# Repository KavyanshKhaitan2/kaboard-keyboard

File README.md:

# Kaboard!
[[ Showcase video ]](https://youtu.be/ID2R_xTHKyI)

_Yet another mechanical keyboard_

This is the first full-size keyboard I built!

It is a full-size mechanical keyboard with LEDs under each key. The firmware is very customisable, you can customise everything using usevia.app.

## Contents
Quickly jump to different sections of this README.
1. [Why?](#why)
1. [Fallout Zine Page](#zine)
1. [PCB](#pcb)
2. [Schematics](#schematics)
3. [Case](#case)
4. [BOM](#bom)
5. [How do I build it?](#how-do-i-build-it)
## Why?
I wanted to learn how to build a keyboard, so this is how I decided to do that!

## Zine

## PCB

[ [View in KiCanvas](https://kicanvas.org/?repo=https://github.com/KavyanshKhaitan2/kaboard-keyboard/tree/main/pcb) ]

## Schematics

## Case
[ [View in Onshape](https://cad.onshape.com/documents/8ed13534193dd50e2cf177a7/w/262d5483b57866700addb319/e/d3e08e0b5eff8c35a30b137c) ] 
### Top

[ [Download STEP file](https://github.com/KavyanshKhaitan2/kaboard-keyboard/raw/refs/heads/main/case/bottom.step) ]
### Bottom

[ [Download STEP file](https://github.com/KavyanshKhaitan2/kaboard-keyboard/raw/refs/heads/main/case/top.step) ]

## BOM
| Item | Qty | Link | Price | Running total |
|------|-----|------|-------|--------------:|
| Keycaps | 1 set |  [StacksKB](https://stackskb.com/store/veekos-gradient-keycaps-cherry-profile-135-keys/) | Rs. 1300 (~ $15) | Rs. 1300 ($15) |
| Switches | 100pc | [CosmicByte](https://www.thecosmicbyte.com/product/gateron-mechanical-switches-compatible-with-cosmic-byte-hot-swappable-keyboards-qty-1pc/) | Rs. 2000 (~ $25) | Rs. 3300 ($40) |
| Resettable Fuse | 1 | [LCSC](https://www.lcsc.com/product-detail/C2153776.html) | $2 (~ Rs. 200) | Rs. 3500 ($42) |
| Raspberry Pi Pico | 1 | [Robu](https://robu.in/product/raspberry-pi-pico/) | Rs. 400 (~ $5) | Rs. 3900 ($47) |
| 1k resistor | 2 | [LCSC](https://www.lcsc.com/product-detail/C119870.html) | $0.60 (~ Rs. 60) | Rs. 3960 ($47.6) |
| 1N4148 diodes | 96 | [LCSC](https://www.lcsc.com/product-detail/C84410.html) | $1.6 (~ Rs. 160) | Rs. 4120 ($49.2) |
| EC11 rotary encoder | 1 | - | 0 | Rs. 4120 ($49.2) |
| SK6812MINI-E | 120 | [LCSC](https://www.lcsc.com/product-detail/C5149201.html?s_z=n_SK6812MINI-E) | $9 (~ Rs. 900) | Rs. 5020 ($58.2) |
| PCB | 1 | AIVON | $25.3 (~Rs. 2300) | Rs. 7320 ($83.5) |
| Keycap Stabilizers | 8 | [StacksKB](https://stackskb.com/store/genuine-cherry-mx-plate-mount-stabilizers-2u/) | Rs. 400 (~$4) | Rs. 7720 ($87.5) |
| Spacebar Stabilizer Wire | 1 | Self fulfilled | Rs. 0 | Rs. 7720 ($87.5) |
| Shipping (Guesstimate) | - | - | $25 (~Rs. 2500) | Rs. 10220 ($112.5) |

## How do I build it?
1. Obtain all of the BoM.
2. Print the 3d case
3. Start soldering the SK6812MINI-Es
4. Solder all the diodes
5. Solder the pi pico from the back
6. Solder the rotary encoder
7. Add the stabilizers to the top part of the case
8. Get the top part of the case and place it over the pcb
9. Get all the switches and place it through the case
10. Solder all the switches that you just placed
11. Plug it in to your computer in BOOTSEL mode
12. Upload the .uf2 firmware file over to the drive that just got mounted
13. Voilla! You are now done!

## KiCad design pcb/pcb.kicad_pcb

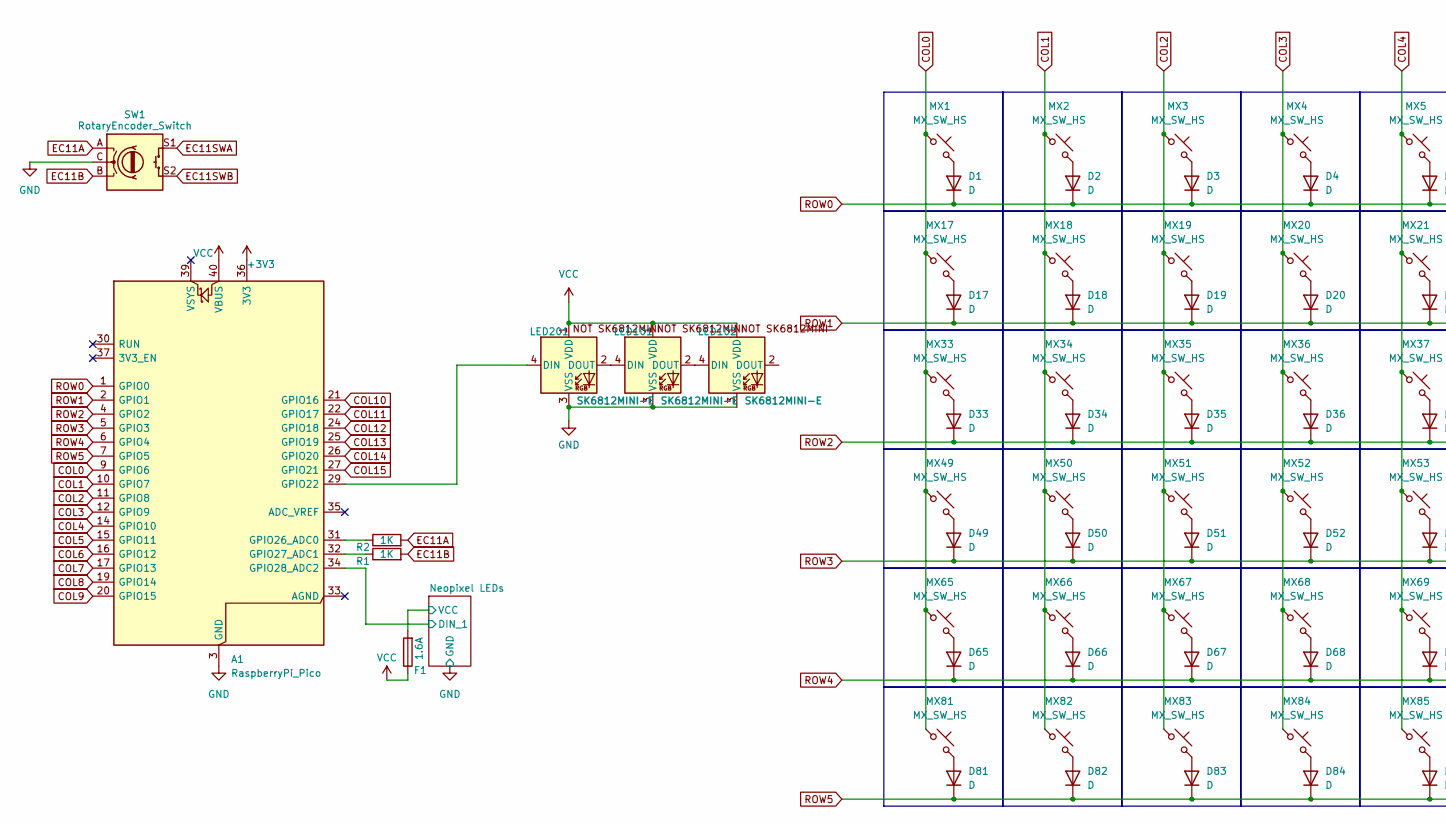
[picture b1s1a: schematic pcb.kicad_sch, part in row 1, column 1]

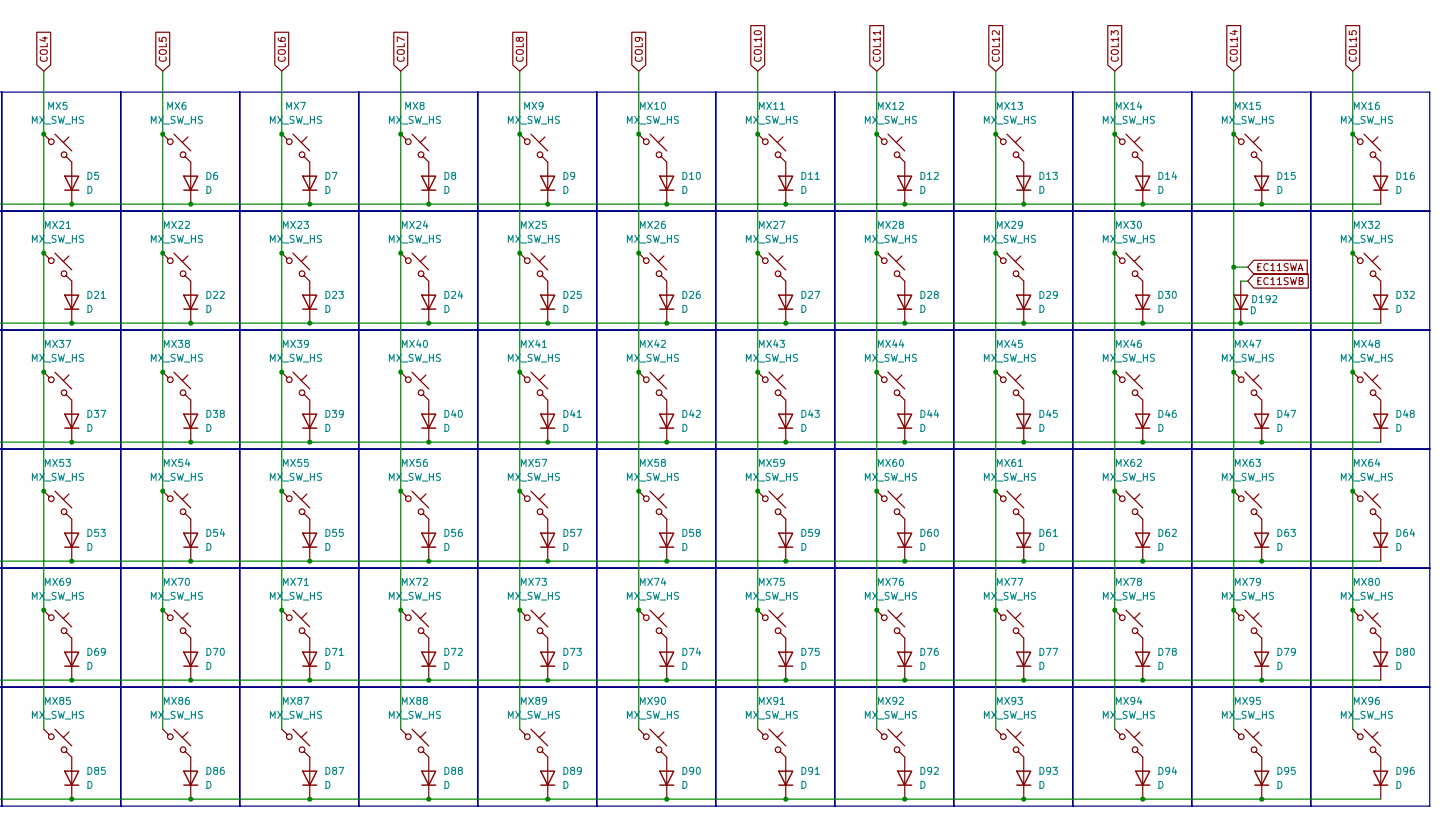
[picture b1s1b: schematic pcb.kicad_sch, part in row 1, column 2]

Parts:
A1: RaspberryPi_Pico; RaspberryPi_Pico_Common_THT
D1, D2, D3, D4, D5, D6, D7, D8, D9, D10, D11, D12, D13, D14, D15, D16, D17, D18, D19, D20, D21, D22, D23, D24, D25, D26, D27, D28, D29, D30, D32, D33, D34, D35, D36, D37, D38, D39, D40, D41, D42, D43, D44, D45, D46, D47, D48, D49, D50, D51, D52, D53, D54, D55, D56, D57, D58, D59, D60, D61, D62, D63, D64, D65, D66, D67, D68, D69, D70, D71, D72, D73, D74, D75, D76, D77, D78, D79, D80, D81, D82, D83, D84, D85, D86, D87, D88, D89, D90, D91, D92, D93, D94, D95, D96, D192: D; D_DO-41_SOD81_P7.62mm_Horizontal
F1: 1.6A; Fuse_Littelfuse_372_D8.50mm
LED101, LED102, LED201: SK6812MINI-E; MX_SK6812MINI-E_REV
MX1, MX2, MX3, MX4, MX5, MX6, MX7, MX8, MX9, MX10, MX11, MX12, MX13, MX14, MX15, MX16, MX17, MX18, MX19, MX20, MX21, MX22, MX23, MX24, MX25, MX26, MX27, MX28, MX29, MX30, MX32, MX33, MX34, MX35, MX36, MX37, MX38, MX39, MX40, MX41, MX42, MX43, MX44, MX45, MX46, MX47, MX48, MX49, MX50, MX51, MX52, MX53, MX54, MX55, MX56, MX57, MX58, MX59, MX60, MX61, MX62, MX63, MX64, MX65, MX66, MX67, MX68, MX69, MX70, MX71, MX72, MX73, MX74, MX75, MX76, MX77, MX78, MX79, MX80, MX81, MX82, MX83, MX84, MX85, MX86, MX87, MX88, MX89, MX90, MX91, MX92, MX93, MX94, MX95, MX96: MX_SW_HS; SW_Cherry_MX_1.00u_PCB_withSwitch
R1, R2: 1K; R_Axial_DIN0204_L3.6mm_D1.6mm_P5.08mm_Horizontal
SW1: RotaryEncoder_Switch; RotaryEncoder_Alps_EC11E-Switch_Vertical_H20mm

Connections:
+3V3: A1.36 (3V3)
/Neopixel LEDs/DIN_1: A1.34 (GPIO28_ADC2); also elsewhere on the board
COL0: A1.9 (GPIO6), MX1.1, MX17.1, MX33.1, MX49.1, MX65.1, MX81.1
COL1: A1.10 (GPIO7), MX2.1, MX18.1, MX34.1, MX50.1, MX66.1, MX82.1
COL2: A1.11 (GPIO8), MX3.1, MX19.1, MX35.1, MX51.1, MX67.1, MX83.1
COL3: A1.12 (GPIO9), MX4.1, MX20.1, MX36.1, MX52.1, MX68.1, MX84.1
COL4: A1.14 (GPIO10), MX5.1, MX21.1, MX37.1, MX53.1, MX69.1, MX85.1
COL5: A1.15 (GPIO11), MX6.1, MX22.1, MX38.1, MX54.1, MX70.1, MX86.1
COL6: A1.16 (GPIO12), MX7.1, MX23.1, MX39.1, MX55.1, MX71.1, MX87.1
COL7: A1.17 (GPIO13), MX8.1, MX24.1, MX40.1, MX56.1, MX72.1, MX88.1
COL8: A1.19 (GPIO14), MX9.1, MX25.1, MX41.1, MX57.1, MX73.1, MX89.1
COL9: A1.20 (GPIO15), MX10.1, MX26.1, MX42.1, MX58.1, MX74.1, MX90.1
COL10: A1.21 (GPIO16), MX11.1, MX27.1, MX43.1, MX59.1, MX75.1, MX91.1
COL11: A1.22 (GPIO17), MX12.1, MX28.1, MX44.1, MX60.1, MX76.1, MX92.1
COL12: A1.24 (GPIO18), MX13.1, MX29.1, MX45.1, MX61.1, MX77.1, MX93.1
COL13: A1.25 (GPIO19), MX14.1, MX30.1, MX46.1, MX62.1, MX78.1, MX94.1
COL14: A1.26 (GPIO20), MX15.1, MX47.1, MX63.1, MX79.1, MX95.1, SW1.S1
COL15: A1.27 (GPIO21), MX16.1, MX32.1, MX48.1, MX64.1, MX80.1, MX96.1
EC11A: R2.2, SW1.A
EC11B: R1.2, SW1.B
EC11SWB: D192.2 (A), SW1.S2
GND: A1.3 (GND), A1.8 (GND), A1.13 (GND), A1.18 (GND), A1.23 (GND), A1.28 (GND), A1.38 (GND), LED101.3 (VSS), LED102.3 (VSS), LED201.3 (VSS), SW1.C; also elsewhere on the board
unnamed: A1.29 (GPIO22), LED201.4 (DIN)
unnamed: A1.31 (GPIO26_ADC0), R2.1
unnamed: A1.32 (GPIO27_ADC1), R1.1
unnamed: D1.2 (A), MX1.2
unnamed: D2.2 (A), MX2.2
unnamed: D3.2 (A), MX3.2
unnamed: D4.2 (A), MX4.2
unnamed: D5.2 (A), MX5.2
unnamed: D6.2 (A), MX6.2
unnamed: D7.2 (A), MX7.2
unnamed: D8.2 (A), MX8.2
unnamed: D9.2 (A), MX9.2
unnamed: D10.2 (A), MX10.2
unnamed: D11.2 (A), MX11.2
unnamed: D12.2 (A), MX12.2
unnamed: D13.2 (A), MX13.2
unnamed: D14.2 (A), MX14.2
unnamed: D15.2 (A), MX15.2
unnamed: D16.2 (A), MX16.2
unnamed: D17.2 (A), MX17.2
unnamed: D18.2 (A), MX18.2
unnamed: D19.2 (A), MX19.2
unnamed: D20.2 (A), MX20.2
unnamed: D21.2 (A), MX21.2
unnamed: D22.2 (A), MX22.2
unnamed: D23.2 (A), MX23.2
unnamed: D24.2 (A), MX24.2
unnamed: D25.2 (A), MX25.2
unnamed: D26.2 (A), MX26.2
unnamed: D27.2 (A), MX27.2
unnamed: D28.2 (A), MX28.2
unnamed: D29.2 (A), MX29.2
unnamed: D30.2 (A), MX30.2
unnamed: D32.2 (A), MX32.2
unnamed: D33.2 (A), MX33.2
unnamed: D34.2 (A), MX34.2
unnamed: D35.2 (A), MX35.2
unnamed: D36.2 (A), MX36.2
unnamed: D37.2 (A), MX37.2
unnamed: D38.2 (A), MX38.2
unnamed: D39.2 (A), MX39.2
unnamed: D40.2 (A), MX40.2
unnamed: D41.2 (A), MX41.2
unnamed: D42.2 (A), MX42.2
unnamed: D43.2 (A), MX43.2
unnamed: D44.2 (A), MX44.2
unnamed: D45.2 (A), MX45.2
unnamed: D46.2 (A), MX46.2
unnamed: D47.2 (A), MX47.2
unnamed: D48.2 (A), MX48.2
unnamed: D49.2 (A), MX49.2
unnamed: D50.2 (A), MX50.2
unnamed: D51.2 (A), MX51.2
unnamed: D52.2 (A), MX52.2
unnamed: D53.2 (A), MX53.2
unnamed: D54.2 (A), MX54.2
unnamed: D55.2 (A), MX55.2
unnamed: D56.2 (A), MX56.2
unnamed: D57.2 (A), MX57.2
unnamed: D58.2 (A), MX58.2
unnamed: D59.2 (A), MX59.2
unnamed: D60.2 (A), MX60.2
unnamed: D61.2 (A), MX61.2
unnamed: D62.2 (A), MX62.2
unnamed: D63.2 (A), MX63.2
unnamed: D64.2 (A), MX64.2
unnamed: D65.2 (A), MX65.2
unnamed: D66.2 (A), MX66.2
unnamed: D67.2 (A), MX67.2
unnamed: D68.2 (A), MX68.2
unnamed: D69.2 (A), MX69.2
unnamed: D70.2 (A), MX70.2
unnamed: D71.2 (A), MX71.2
unnamed: D72.2 (A), MX72.2
unnamed: D73.2 (A), MX73.2
unnamed: D74.2 (A), MX74.2
unnamed: D75.2 (A), MX75.2
unnamed: D76.2 (A), MX76.2
unnamed: D77.2 (A), MX77.2
unnamed: D78.2 (A), MX78.2
unnamed: D79.2 (A), MX79.2
unnamed: D80.2 (A), MX80.2
unnamed: D81.2 (A), MX81.2
unnamed: D82.2 (A), MX82.2
unnamed: D83.2 (A), MX83.2
unnamed: D84.2 (A), MX84.2
unnamed: D85.2 (A), MX85.2
unnamed: D86.2 (A), MX86.2
unnamed: D87.2 (A), MX87.2
unnamed: D88.2 (A), MX88.2
unnamed: D89.2 (A), MX89.2
unnamed: D90.2 (A), MX90.2
unnamed: D91.2 (A), MX91.2
unnamed: D92.2 (A), MX92.2
unnamed: D93.2 (A), MX93.2
unnamed: D94.2 (A), MX94.2
unnamed: D95.2 (A), MX95.2
unnamed: D96.2 (A), MX96.2
unnamed: LED101.4 (DIN), LED201.2 (DOUT)
unnamed: LED101.2 (DOUT), LED102.4 (DIN)
ROW0: A1.1 (GPIO0), D1.1 (K), D2.1 (K), D3.1 (K), D4.1 (K), D5.1 (K), D6.1 (K), D7.1 (K), D8.1 (K), D9.1 (K), D10.1 (K), D11.1 (K), D12.1 (K), D13.1 (K), D14.1 (K), D15.1 (K), D16.1 (K)
ROW1: A1.2 (GPIO1), D17.1 (K), D18.1 (K), D19.1 (K), D20.1 (K), D21.1 (K), D22.1 (K), D23.1 (K), D24.1 (K), D25.1 (K), D26.1 (K), D27.1 (K), D28.1 (K), D29.1 (K), D30.1 (K), D32.1 (K), D192.1 (K)
ROW2: A1.4 (GPIO2), D33.1 (K), D34.1 (K), D35.1 (K), D36.1 (K), D37.1 (K), D38.1 (K), D39.1 (K), D40.1 (K), D41.1 (K), D42.1 (K), D43.1 (K), D44.1 (K), D45.1 (K), D46.1 (K), D47.1 (K), D48.1 (K)
ROW3: A1.5 (GPIO3), D49.1 (K), D50.1 (K), D51.1 (K), D52.1 (K), D53.1 (K), D54.1 (K), D55.1 (K), D56.1 (K), D57.1 (K), D58.1 (K), D59.1 (K), D60.1 (K), D61.1 (K), D62.1 (K), D63.1 (K), D64.1 (K)
ROW4: A1.6 (GPIO4), D65.1 (K), D66.1 (K), D67.1 (K), D68.1 (K), D69.1 (K), D70.1 (K), D71.1 (K), D72.1 (K), D73.1 (K), D74.1 (K), D75.1 (K), D76.1 (K), D77.1 (K), D78.1 (K), D79.1 (K), D80.1 (K)
ROW5: A1.7 (GPIO5), D81.1 (K), D82.1 (K), D83.1 (K), D84.1 (K), D85.1 (K), D86.1 (K), D87.1 (K), D88.1 (K), D89.1 (K), D90.1 (K), D91.1 (K), D92.1 (K), D93.1 (K), D94.1 (K), D95.1 (K), D96.1 (K)
VCC: A1.40 (VBUS), F1.1, F1.2, LED101.1 (VDD), LED102.1 (VDD), LED201.1 (VDD); also elsewhere on the board

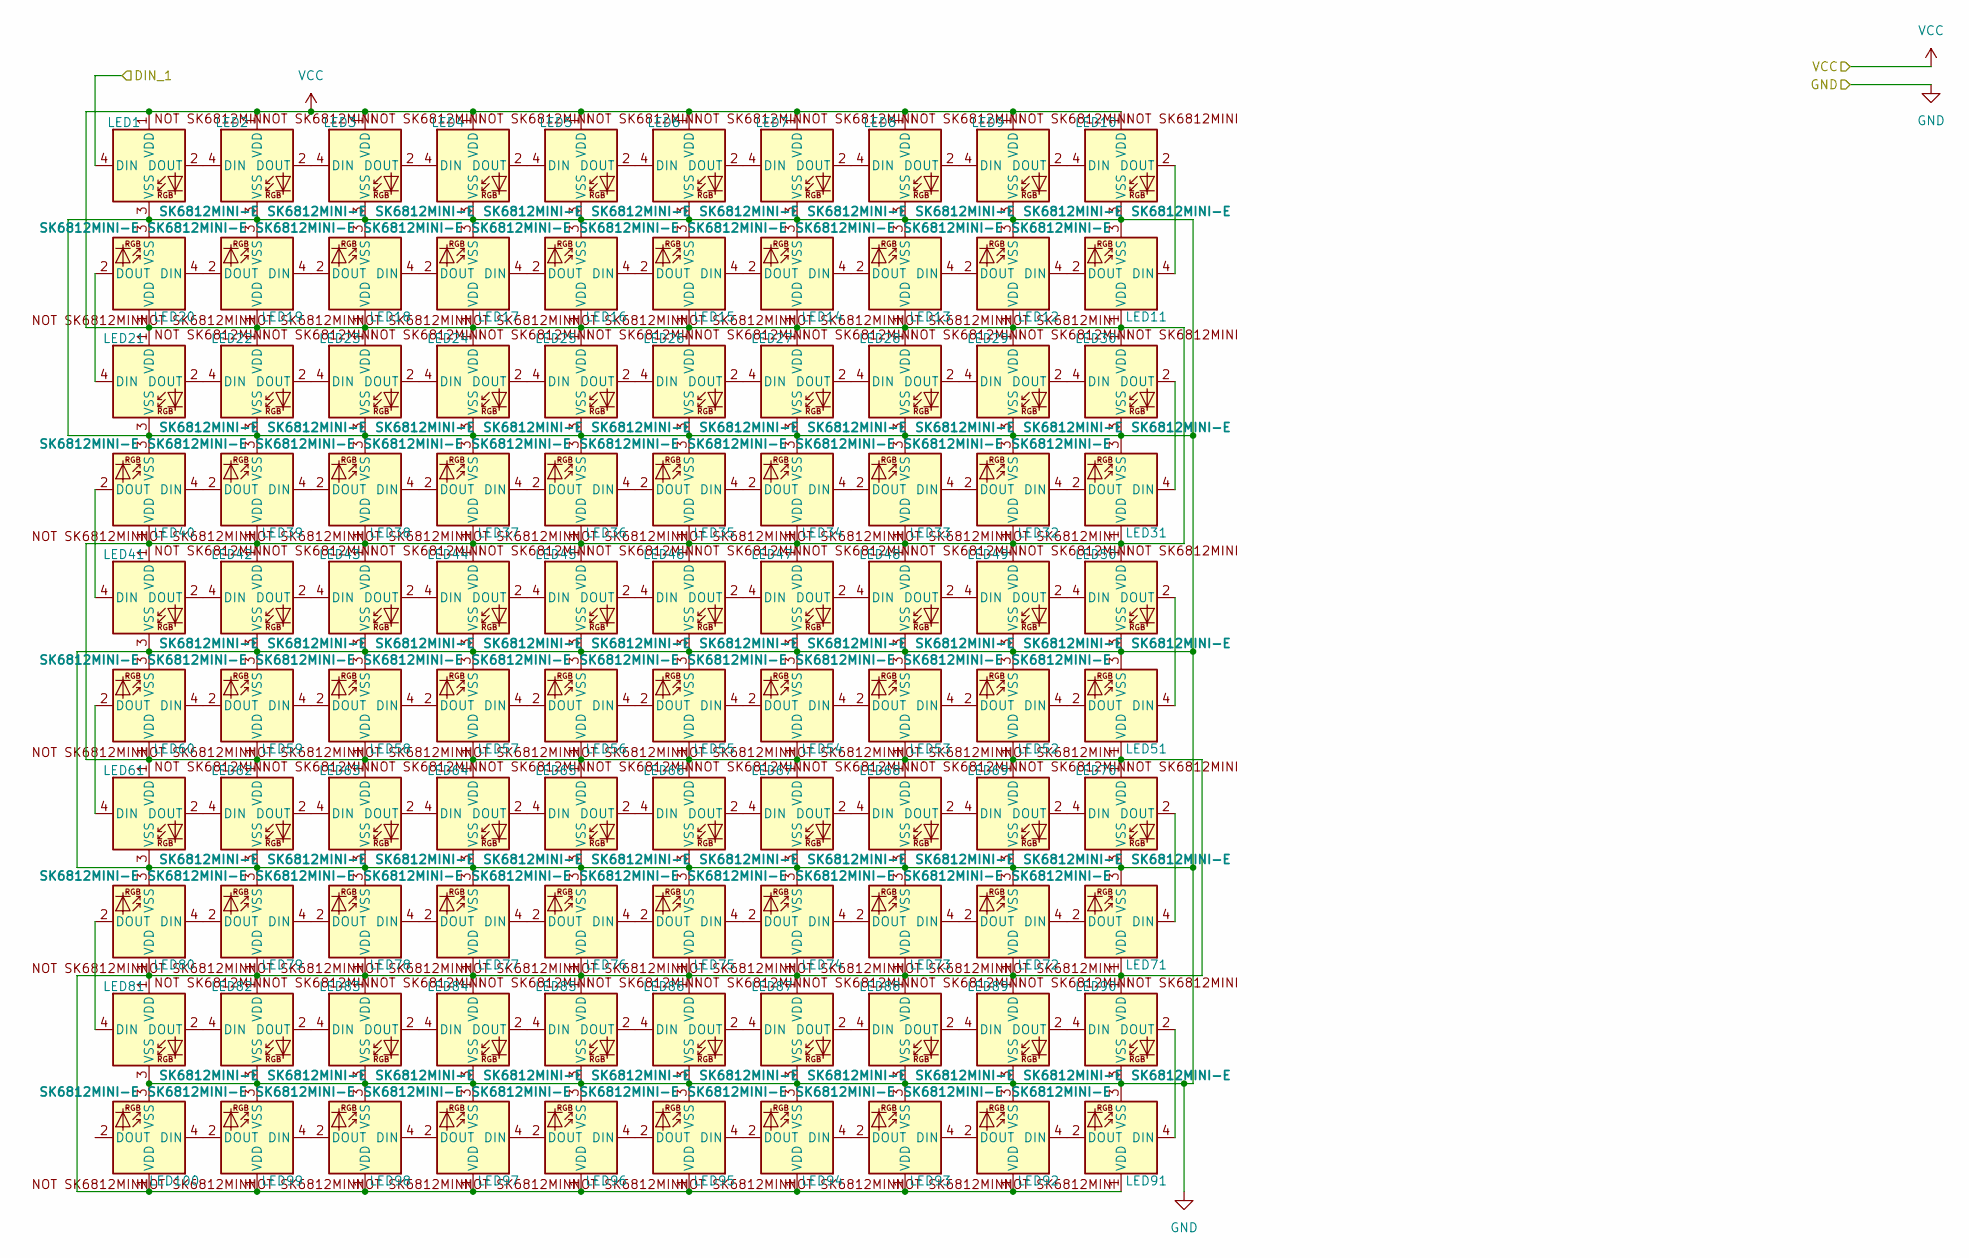
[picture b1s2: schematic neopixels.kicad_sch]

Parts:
LED1, LED2, LED3, LED4, LED5, LED6, LED7, LED8, LED9, LED10, LED11, LED12, LED13, LED14, LED15, LED16, LED17, LED18, LED19, LED20, LED21, LED22, LED23, LED24, LED25, LED26, LED27, LED28, LED29, LED30, LED31, LED32, LED33, LED34, LED35, LED36, LED37, LED38, LED39, LED40, LED41, LED42, LED43, LED44, LED45, LED46, LED47, LED48, LED49, LED50, LED51, LED52, LED53, LED54, LED55, LED56, LED57, LED58, LED59, LED60, LED61, LED62, LED63, LED64, LED65, LED66, LED67, LED68, LED69, LED70, LED71, LED72, LED73, LED74, LED75, LED76, LED77, LED78, LED79, LED80, LED81, LED82, LED83, LED84, LED85, LED86, LED87, LED88, LED89, LED90, LED91, LED92, LED93, LED94, LED95, LED96, LED97, LED98, LED99, LED100: SK6812MINI-E; MX_SK6812MINI-E_REV

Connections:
/Neopixel LEDs/DIN_1: LED1.4 (DIN); also elsewhere on the board
GND: LED1.3 (VSS), LED2.3 (VSS), LED3.3 (VSS), LED4.3 (VSS), LED5.3 (VSS), LED6.3 (VSS), LED7.3 (VSS), LED8.3 (VSS), LED9.3 (VSS), LED10.3 (VSS), LED11.3 (VSS), LED12.3 (VSS), LED13.3 (VSS), LED14.3 (VSS), LED15.3 (VSS), LED16.3 (VSS), LED17.3 (VSS), LED18.3 (VSS), LED19.3 (VSS), LED20.3 (VSS), LED21.3 (VSS), LED22.3 (VSS), LED23.3 (VSS), LED24.3 (VSS), LED25.3 (VSS), LED26.3 (VSS), LED27.3 (VSS), LED28.3 (VSS), LED29.3 (VSS), LED30.3 (VSS), LED31.3 (VSS), LED32.3 (VSS), LED33.3 (VSS), LED34.3 (VSS), LED35.3 (VSS), LED36.3 (VSS), LED37.3 (VSS), LED38.3 (VSS), LED39.3 (VSS), LED40.3 (VSS), LED41.3 (VSS), LED42.3 (VSS), LED43.3 (VSS), LED44.3 (VSS), LED45.3 (VSS), LED46.3 (VSS), LED47.3 (VSS), LED48.3 (VSS), LED49.3 (VSS), LED50.3 (VSS), LED51.3 (VSS), LED52.3 (VSS), LED53.3 (VSS), LED54.3 (VSS), LED55.3 (VSS), LED56.3 (VSS), LED57.3 (VSS), LED58.3 (VSS), LED59.3 (VSS), LED60.3 (VSS), LED61.3 (VSS), LED62.3 (VSS), LED63.3 (VSS), LED64.3 (VSS), LED65.3 (VSS), LED66.3 (VSS), LED67.3 (VSS), LED68.3 (VSS), LED69.3 (VSS), LED70.3 (VSS), LED71.3 (VSS), LED72.3 (VSS), LED73.3 (VSS), LED74.3 (VSS), LED75.3 (VSS), LED76.3 (VSS), LED77.3 (VSS), LED78.3 (VSS), LED79.3 (VSS), LED80.3 (VSS), LED81.3 (VSS), LED82.3 (VSS), LED83.3 (VSS), LED84.3 (VSS), LED85.3 (VSS), LED86.3 (VSS), LED87.3 (VSS), LED88.3 (VSS), LED89.3 (VSS), LED90.3 (VSS), LED91.3 (VSS), LED92.3 (VSS), LED93.3 (VSS), LED94.3 (VSS), LED95.3 (VSS), LED96.3 (VSS), LED97.3 (VSS), LED98.3 (VSS), LED99.3 (VSS), LED100.3 (VSS); also elsewhere on the board
unnamed: LED1.2 (DOUT), LED2.4 (DIN)
unnamed: LED2.2 (DOUT), LED3.4 (DIN)
unnamed: LED3.2 (DOUT), LED4.4 (DIN)
unnamed: LED4.2 (DOUT), LED5.4 (DIN)
unnamed: LED5.2 (DOUT), LED6.4 (DIN)
unnamed: LED6.2 (DOUT), LED7.4 (DIN)
unnamed: LED7.2 (DOUT), LED8.4 (DIN)
unnamed: LED8.2 (DOUT), LED9.4 (DIN)
unnamed: LED9.2 (DOUT), LED10.4 (DIN)
unnamed: LED10.2 (DOUT), LED11.4 (DIN)
unnamed: LED11.2 (DOUT), LED12.4 (DIN)
unnamed: LED12.2 (DOUT), LED13.4 (DIN)
unnamed: LED13.2 (DOUT), LED14.4 (DIN)
unnamed: LED14.2 (DOUT), LED15.4 (DIN)
unnamed: LED15.2 (DOUT), LED16.4 (DIN)
unnamed: LED16.2 (DOUT), LED17.4 (DIN)
unnamed: LED17.2 (DOUT), LED18.4 (DIN)
unnamed: LED18.2 (DOUT), LED19.4 (DIN)
unnamed: LED19.2 (DOUT), LED20.4 (DIN)
unnamed: LED20.2 (DOUT), LED21.4 (DIN)
unnamed: LED21.2 (DOUT), LED22.4 (DIN)
unnamed: LED22.2 (DOUT), LED23.4 (DIN)
unnamed: LED23.2 (DOUT), LED24.4 (DIN)
unnamed: LED24.2 (DOUT), LED25.4 (DIN)
unnamed: LED25.2 (DOUT), LED26.4 (DIN)
unnamed: LED26.2 (DOUT), LED27.4 (DIN)
unnamed: LED27.2 (DOUT), LED28.4 (DIN)
unnamed: LED28.2 (DOUT), LED29.4 (DIN)
unnamed: LED29.2 (DOUT), LED30.4 (DIN)
unnamed: LED30.2 (DOUT), LED31.4 (DIN)
unnamed: LED31.2 (DOUT), LED32.4 (DIN)
unnamed: LED32.2 (DOUT), LED33.4 (DIN)
unnamed: LED33.2 (DOUT), LED34.4 (DIN)
unnamed: LED34.2 (DOUT), LED35.4 (DIN)
unnamed: LED35.2 (DOUT), LED36.4 (DIN)
unnamed: LED36.2 (DOUT), LED37.4 (DIN)
unnamed: LED37.2 (DOUT), LED38.4 (DIN)
unnamed: LED38.2 (DOUT), LED39.4 (DIN)
unnamed: LED39.2 (DOUT), LED40.4 (DIN)
unnamed: LED40.2 (DOUT), LED41.4 (DIN)
unnamed: LED41.2 (DOUT), LED42.4 (DIN)
unnamed: LED42.2 (DOUT), LED43.4 (DIN)
unnamed: LED43.2 (DOUT), LED44.4 (DIN)
unnamed: LED44.2 (DOUT), LED45.4 (DIN)
unnamed: LED45.2 (DOUT), LED46.4 (DIN)
unnamed: LED46.2 (DOUT), LED47.4 (DIN)
unnamed: LED47.2 (DOUT), LED48.4 (DIN)
unnamed: LED48.2 (DOUT), LED49.4 (DIN)
unnamed: LED49.2 (DOUT), LED50.4 (DIN)
unnamed: LED50.2 (DOUT), LED51.4 (DIN)
unnamed: LED51.2 (DOUT), LED52.4 (DIN)
unnamed: LED52.2 (DOUT), LED53.4 (DIN)
unnamed: LED53.2 (DOUT), LED54.4 (DIN)
unnamed: LED54.2 (DOUT), LED55.4 (DIN)
unnamed: LED55.2 (DOUT), LED56.4 (DIN)
unnamed: LED56.2 (DOUT), LED57.4 (DIN)
unnamed: LED57.2 (DOUT), LED58.4 (DIN)
unnamed: LED58.2 (DOUT), LED59.4 (DIN)
unnamed: LED59.2 (DOUT), LED60.4 (DIN)
unnamed: LED60.2 (DOUT), LED61.4 (DIN)
unnamed: LED61.2 (DOUT), LED62.4 (DIN)
unnamed: LED62.2 (DOUT), LED63.4 (DIN)
unnamed: LED63.2 (DOUT), LED64.4 (DIN)
unnamed: LED64.2 (DOUT), LED65.4 (DIN)
unnamed: LED65.2 (DOUT), LED66.4 (DIN)
unnamed: LED66.2 (DOUT), LED67.4 (DIN)
unnamed: LED67.2 (DOUT), LED68.4 (DIN)
unnamed: LED68.2 (DOUT), LED69.4 (DIN)
unnamed: LED69.2 (DOUT), LED70.4 (DIN)
unnamed: LED70.2 (DOUT), LED71.4 (DIN)
unnamed: LED71.2 (DOUT), LED72.4 (DIN)
unnamed: LED72.2 (DOUT), LED73.4 (DIN)
unnamed: LED73.2 (DOUT), LED74.4 (DIN)
unnamed: LED74.2 (DOUT), LED75.4 (DIN)
unnamed: LED75.2 (DOUT), LED76.4 (DIN)
unnamed: LED76.2 (DOUT), LED77.4 (DIN)
unnamed: LED77.2 (DOUT), LED78.4 (DIN)
unnamed: LED78.2 (DOUT), LED79.4 (DIN)
unnamed: LED79.2 (DOUT), LED80.4 (DIN)
unnamed: LED80.2 (DOUT), LED81.4 (DIN)
unnamed: LED81.2 (DOUT), LED82.4 (DIN)
unnamed: LED82.2 (DOUT), LED83.4 (DIN)
unnamed: LED83.2 (DOUT), LED84.4 (DIN)
unnamed: LED84.2 (DOUT), LED85.4 (DIN)
unnamed: LED85.2 (DOUT), LED86.4 (DIN)
unnamed: LED86.2 (DOUT), LED87.4 (DIN)
unnamed: LED87.2 (DOUT), LED88.4 (DIN)
unnamed: LED88.2 (DOUT), LED89.4 (DIN)
unnamed: LED89.2 (DOUT), LED90.4 (DIN)
unnamed: LED90.2 (DOUT), LED91.4 (DIN)
unnamed: LED91.2 (DOUT), LED92.4 (DIN)
unnamed: LED92.2 (DOUT), LED93.4 (DIN)
unnamed: LED93.2 (DOUT), LED94.4 (DIN)
unnamed: LED94.2 (DOUT), LED95.4 (DIN)
unnamed: LED95.2 (DOUT), LED96.4 (DIN)
unnamed: LED96.2 (DOUT), LED97.4 (DIN)
unnamed: LED97.2 (DOUT), LED98.4 (DIN)
unnamed: LED98.2 (DOUT), LED99.4 (DIN)
unnamed: LED99.2 (DOUT), LED100.4 (DIN)
VCC: LED1.1 (VDD), LED2.1 (VDD), LED3.1 (VDD), LED4.1 (VDD), LED5.1 (VDD), LED6.1 (VDD), LED7.1 (VDD), LED8.1 (VDD), LED9.1 (VDD), LED10.1 (VDD), LED11.1 (VDD), LED12.1 (VDD), LED13.1 (VDD), LED14.1 (VDD), LED15.1 (VDD), LED16.1 (VDD), LED17.1 (VDD), LED18.1 (VDD), LED19.1 (VDD), LED20.1 (VDD), LED21.1 (VDD), LED22.1 (VDD), LED23.1 (VDD), LED24.1 (VDD), LED25.1 (VDD), LED26.1 (VDD), LED27.1 (VDD), LED28.1 (VDD), LED29.1 (VDD), LED30.1 (VDD), LED31.1 (VDD), LED32.1 (VDD), LED33.1 (VDD), LED34.1 (VDD), LED35.1 (VDD), LED36.1 (VDD), LED37.1 (VDD), LED38.1 (VDD), LED39.1 (VDD), LED40.1 (VDD), LED41.1 (VDD), LED42.1 (VDD), LED43.1 (VDD), LED44.1 (VDD), LED45.1 (VDD), LED46.1 (VDD), LED47.1 (VDD), LED48.1 (VDD), LED49.1 (VDD), LED50.1 (VDD), LED51.1 (VDD), LED52.1 (VDD), LED53.1 (VDD), LED54.1 (VDD), LED55.1 (VDD), LED56.1 (VDD), LED57.1 (VDD), LED58.1 (VDD), LED59.1 (VDD), LED60.1 (VDD), LED61.1 (VDD), LED62.1 (VDD), LED63.1 (VDD), LED64.1 (VDD), LED65.1 (VDD), LED66.1 (VDD), LED67.1 (VDD), LED68.1 (VDD), LED69.1 (VDD), LED70.1 (VDD), LED71.1 (VDD), LED72.1 (VDD), LED73.1 (VDD), LED74.1 (VDD), LED75.1 (VDD), LED76.1 (VDD), LED77.1 (VDD), LED78.1 (VDD), LED79.1 (VDD), LED80.1 (VDD), LED81.1 (VDD), LED82.1 (VDD), LED83.1 (VDD), LED84.1 (VDD), LED85.1 (VDD), LED86.1 (VDD), LED87.1 (VDD), LED88.1 (VDD), LED89.1 (VDD), LED90.1 (VDD), LED91.1 (VDD), LED92.1 (VDD), LED93.1 (VDD), LED94.1 (VDD), LED95.1 (VDD), LED96.1 (VDD), LED97.1 (VDD), LED98.1 (VDD), LED99.1 (VDD), LED100.1 (VDD); also elsewhere on the board

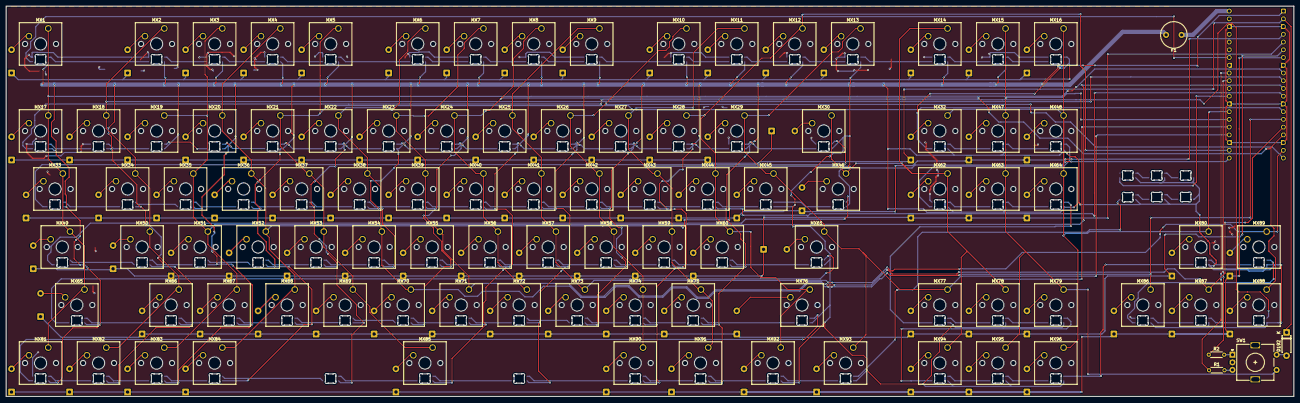
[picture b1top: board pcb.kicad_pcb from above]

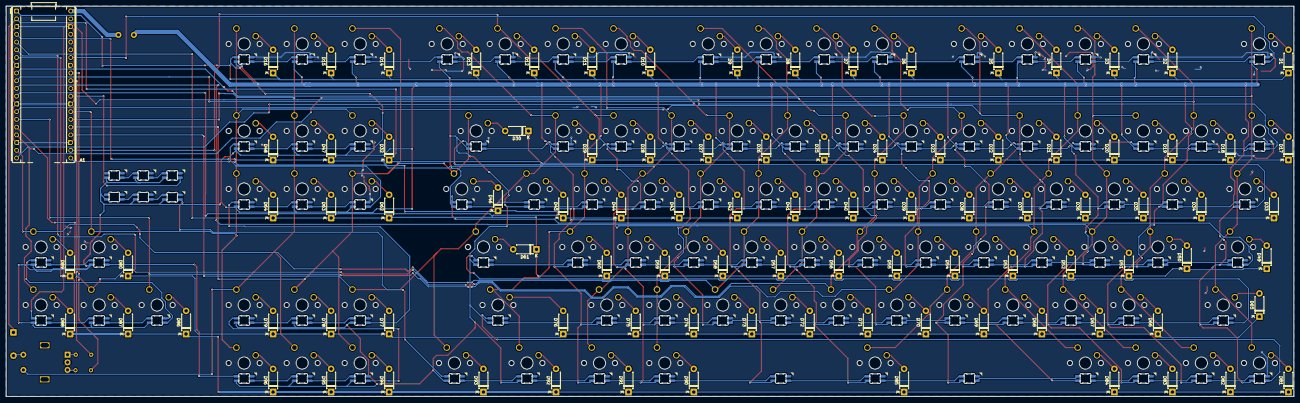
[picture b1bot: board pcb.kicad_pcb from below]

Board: 2 copper layers, 422.8 x 128.1 mm, 299 parts (96 on the bottom side), 227 nets.

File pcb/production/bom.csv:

Designator,Footprint,Quantity,Value,LCSC Part #
A1,RaspberryPi_Pico_Common_THT,1,RaspberryPi_Pico,
"D1, D10, D11, D12, D13, D14, D15, D16, D17, D18, D19, D192, D2, D20, D21, D22, D23, D24, D25, D26, D27, D28, D29, D3, D30, D32, D33, D34, D35, D36, D37, D38, D39, D4, D40, D41, D42, D43, D44, D45, D46, D47, D48, D49, D5, D50, D51, D52, D53, D54, D55, D56, D57, D58, D59, D6, D60, D61, D62, D63, D64, D65, D66, D67, D68, D69, D7, D70, D71, D72, D73, D74, D75, D76, D77, D78, D79, D8, D80, D81, D82, D83, D84, D85, D86, D87, D88, D89, D9, D90, D91, D92, D93, D94, D95, D96",D_DO-41_SOD81_P7.62mm_Horizontal,96,D,
F1,Fuse_Littelfuse_372_D8.50mm,1,1.6A,
"LED1, LED10, LED100, LED101, LED102, LED11, LED12, LED13, LED14, LED15, LED16, LED17, LED18, LED19, LED2, LED20, LED201, LED21, LED22, LED23, LED24, LED25, LED26, LED27, LED28, LED29, LED3, LED30, LED31, LED32, LED33, LED34, LED35, LED36, LED37, LED38, LED39, LED4, LED40, LED41, LED42, LED43, LED44, LED45, LED46, LED47, LED48, LED49, LED5, LED50, LED51, LED52, LED53, LED54, LED55, LED56, LED57, LED58, LED59, LED6, LED60, LED61, LED62, LED63, LED64, LED65, LED66, LED67, LED68, LED69, LED7, LED70, LED71, LED72, LED73, LED74, LED75, LED76, LED77, LED78, LED79, LED8, LED80, LED81, LED82, LED83, LED84, LED85, LED86, LED87, LED88, LED89, LED9, LED90, LED91, LED92, LED93, LED94, LED95, LED96, LED97, LED98, LED99",MX_SK6812MINI-E_REV,103,SK6812MINI-E,
"MX1, MX10, MX11, MX12, MX13, MX14, MX15, MX16, MX17, MX18, MX19, MX2, MX20, MX21, MX22, MX23, MX24, MX25, MX26, MX27, MX28, MX29, MX3, MX30, MX32, MX33, MX34, MX35, MX36, MX37, MX38, MX39, MX4, MX40, MX41, MX42, MX43, MX44, MX45, MX46, MX47, MX48, MX49, MX5, MX50, MX51, MX52, MX53, MX54, MX55, MX56, MX57, MX58, MX59, MX6, MX60, MX61, MX62, MX63, MX64, MX65, MX66, MX67, MX68, MX69, MX7, MX70, MX71, MX72, MX73, MX74, MX75, MX76, MX77, MX78, MX79, MX8, MX80, MX81, MX82, MX83, MX84, MX85, MX86, MX87, MX88, MX89, MX9, MX90, MX91, MX92, MX93, MX94, MX95, MX96",SW_Cherry_MX_1.00u_PCB_withSwitch,95,MX_SW_HS,
"R1, R2",R_Axial_DIN0204_L3.6mm_D1.6mm_P5.08mm_Horizontal,2,1K,
SW1,RotaryEncoder_Alps_EC11E-Switch_Vertical_H20mm,1,RotaryEncoder_Switch,

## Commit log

2026-03-06 init
2026-03-06 Update IBOM
2026-03-06 Update BOM
2026-03-06 Added gerbers
2026-03-07 Ready for submission
2026-03-17 Updated PCB slightly
2026-05-11 Add Zine section and link to README
2026-05-11 Added the Zine PDF
2026-05-11 Add showcase video link to README
2026-05-27 Added new firmware
